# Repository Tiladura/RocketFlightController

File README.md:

# RocketFlightController
I decided to design a custom flight controller because i wanted to learn more about custom PCBs and overall sensors and microcontrollers workflow, while trying to master soldering along the way :p

## Components
- **ESP32-WROOM-32E** - i used this module in Kicad, it is a great microcontroller which can be accessed remotely because of its wifi/bluetooth modules.
- **BMP280** - pressure sensor which can be used to approximate height which is crucial for drones, rockets and etc.
- **MPU-6050** - simple accelerometer which also has a gyroscope used to determine tilt/angle
I also decided to make spaces or pins for 4 servos, as i planned to allocate 2 of them for TVC(thrust vector control), and other 2 for an active recovery system.

And there is a bunch of capacitors, resistors, some buttons which are all used on a single custom PCB, all parts of which i will list in BOM list in the end.

### The entire board can be powered from a standard 5 V battery pack or USB power bank. I did not include it in the BOM because it is a common off-the-shelf item that users can easily purchase separately.
## Electronics and PCB

| Schematic | PCB Layout | 3D Render |
|----------|------------|-----------|
|  |  |  |

All parts will be hand soldered by me. PCB contains smd and tht components:

## BOM List

| Name | Purpose | Qty | Total (USD) | Link | Distributor |
|---|---|---:|---:|---|---|
|Custom PCB|Plate which will store and connect all components|5|2|--|JLCPCB|
| 03EC0575 (C2831775) | Large servo rail capacitor to reduce voltage dips during servo movement. | 10 | 0.47 | [Link](https://www.lcsc.com/product-detail/C2831775.html) | LCSC |
| DB128L-5.08-2P-GN-S (C395868) | Power input terminals for logic and servo power connections. | 5 | 0.99 | [Link](https://www.lcsc.com/product-detail/C395868.html) | LCSC |
| 2.54-1*3P (C49257) | 3-pin servo headers for servo power, ground, and PWM signal. | 50 | 1.06 | [Link](https://www.lcsc.com/product-detail/C49257.html) | LCSC |
| 2.54-1x6P (C37208) | UART programming header for flashing and debugging the ESP32. | 20 | 0.88 | [Link](https://www.lcsc.com/product-detail/C37208.html) | LCSC |
| 1206B106K500NT (C303950) | Bulk/decoupling capacitors for the stable 3.3 V regulator input/output and logic power. | 5 | 0.43 | [Link](https://www.lcsc.com/product-detail/C303950.html) | LCSC |
| 0805W8F4701T5E (C17673) | I2C pull-up resistors for SDA and SCL lines. | 100 | 0.22 | [Link](https://www.lcsc.com/product-detail/C17673.html) | LCSC |
| 0805W8F1002T5E (C17414) | Pull-up/pull-down resistors for ESP32 boot/reset and sensor address configuration. | 100 | 0.30 | [Link](https://www.lcsc.com/product-detail/C17414.html) | LCSC |
| ESP32-WROOM-32E-N8 (C701342) | Main microcontroller module for sensor reading, servo control, and wireless debugging. | 1 | 4.42 | [Link](https://www.lcsc.com/product-detail/C701342.html) | LCSC |
| MPU-6050 (C24112) | IMU sensor for acceleration and angular velocity measurement during rocket flight. | 1 | 9.99 | [Link](https://www.lcsc.com/product-detail/C24112.html) | LCSC |
| BMP280 (C83291) | Barometric pressure sensor for altitude and pressure measurement. | 1 | 6.03 | [Link](https://www.lcsc.com/product-detail/C83291.html) | LCSC |
| CC0805KRX7R9BB104 (C49678) | Decoupling capacitors for the ESP32, MPU6050, BMP280, and power rail noise filtering. | 100 | 0.53 | [Link](https://www.lcsc.com/product-detail/C49678.html) | LCSC |
| AMS1117-3.3 (C6186) | 3.3 V voltage regulator for the ESP32 and sensors. | 5 | 1.07 | [Link](https://www.lcsc.com/product-detail/C6186.html) | LCSC |
| TL1105AF160Q (C273465) | Reset and boot tactile buttons for programming and manual restart. | 5 | 0.48 | [Link](https://www.lcsc.com/product-detail/C273465.html) | LCSC |

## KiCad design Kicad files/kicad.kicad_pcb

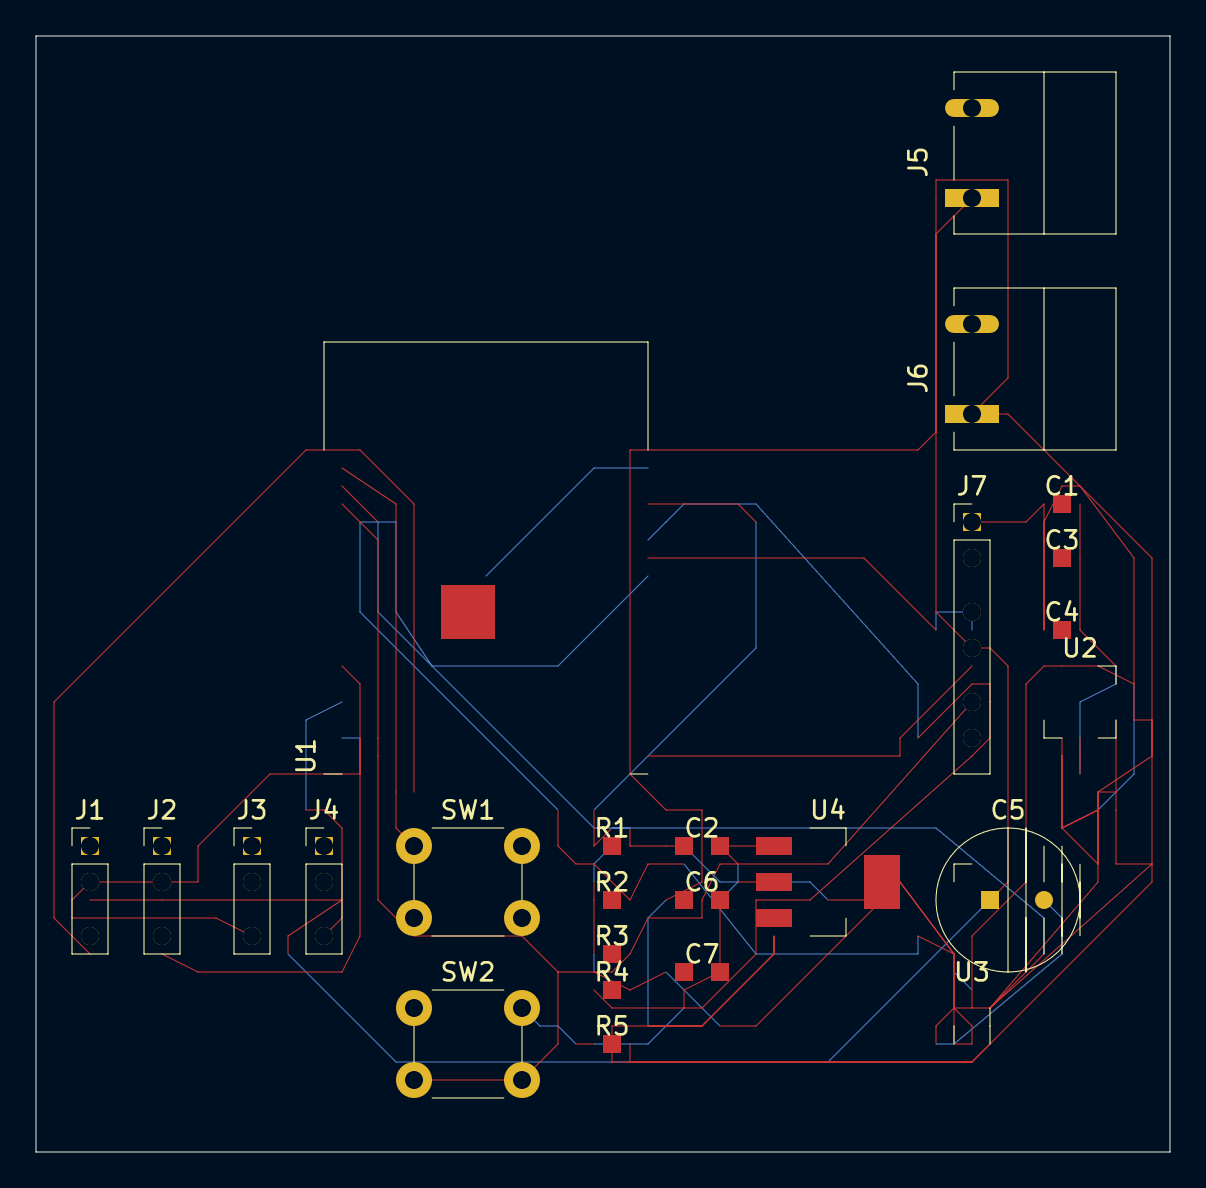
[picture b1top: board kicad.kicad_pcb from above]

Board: 2 copper layers, 63.0 x 62.0 mm, 25 parts (0 on the bottom side), 15 nets.

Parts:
C1, C3, C4: 100n; C_0805_2012Metric
C2, C6, C7: 10u; C_1206_3216Metric
C5: 470u; CP_Radial_D8.0mm_P3.50mm
J1, J2, J3, J4: Conn_01x03_Pin; PinHeader_1x03_P2.54mm_Vertical
J5: SERVO_POWER_IN; PhoenixContact_MC_1,5_2-G-5.08_1x02_P5.08mm_Horizontal
J6: LOGIC_POWER_IN; PhoenixContact_MC_1,5_2-G-5.08_1x02_P5.08mm_Horizontal
J7: UART_PROGRAM; PinHeader_1x06_P2.54mm_Vertical
R1, R2: 4.7k; R_0805_2012Metric
R3, R4, R5: 10k; R_0805_2012Metric
SW1: RESET; SW_PUSH_6mm
SW2: BOOT; SW_PUSH_6mm
U1: ESP32-WROOM-32E; ESP32-WROOM-32D
U2: MPU-6050; InvenSense_QFN-24_4x4mm_P0.5mm
U3: BMP280; Bosch_LGA-8_2x2.5mm_P0.65mm_ClockwisePinNumbering
U4: AMS1117-3.3; SOT-223-3_TabPin2

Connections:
+3V3: C1.1, C2.1, C3.1, C4.1, C7.1, J7.1, R1.2, R2.1, R3.1, R4.2, U1.2 (VDD), U2.8 (VLOGIC), U2.13 (VDD), U3.2 (CSB), U3.6 (VDDIO), U3.8 (VDD), U4.2 (VO)
+5V: C6.1, J6.1, U4.3 (VI)
EN: J7.5, R3.2, SW1.2, SW2.2, U1.3 (EN)
GND: C1.2, C2.2, C3.2, C4.2, C5.2, C6.2, C7.2, J1.1, J2.1, J3.1, J4.1, J5.2, J6.2, J7.2, R5.1, SW1.1, SW2.1, U1.1 (GND), U1.15 (GND), U1.38 (GND), U1.39 (GND), U2.9 (AD0), U2.11 (FSYNC), U2.18 (GND), U3.1 (GND), U3.7 (GND), U4.1 (GND)
IO0: J7.4, U1.25 (IO0)
unnamed: R5.2, U3.5 (SDO)
RXd0/IO3: J7.3, U1.34 (RXD0/IO3)
SERVO5V: C5.1, J1.2, J2.2, J3.2, J4.2, J5.1
SERVO_1: J1.3, U1.16 (IO13)
SERVO_2: J2.3, U1.13 (IO14)
SERVO_3: J3.3, U1.10 (IO25)
SERVO_4: J4.3, U1.11 (IO26)
TXD0/IO1: J7.6, R4.1, U1.35 (TXD0/IO1)
io21: R2.2, U1.33 (IO21), U2.24 (SDA), U3.3 (SDI)
io22: R1.1, U1.36 (IO22), U2.23 (SCL), U3.4 (SCK)

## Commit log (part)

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2026-06-16 Create temp
2026-06-16 Add PCB render image to README
2026-06-16 Replace PCB render image with new version
    Updated PCB render image in README.
